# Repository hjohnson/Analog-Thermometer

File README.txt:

PHYS 320 Final Project: Thermometer. 
Harry Johnson
12/17/11
CC BY/SA 3.0

	These circuits are a paired temperature probe and analog panel meter to display said temperature.
 	
	On the probe side, a 2n3904 NPN transistor is used in saturation, where the Base-Emitter junction is essentially a diode. Silicon diodes in saturation have a fairly linear -2.2mV/ºC temperature coefficient. The forward voltage is also dependent on the collector current of the transistor, so the transistor is immersed in ice water to cool it to 0ºC and a potentiometer is used to calibrate the forward voltage to equal a reference voltage formed by R1 and R2. When this is done, the op amp will output 0 volts when the temperature is 0ºC. Next, a second potentiometer is used to calibrate the gain of the op amp circuit so an increase in 1ºC results in a voltage output increase of 100mV.

	On the panel meter side, a 0-100mA ammeter driven by a standard op amp current source is used to display 0-100ºC.

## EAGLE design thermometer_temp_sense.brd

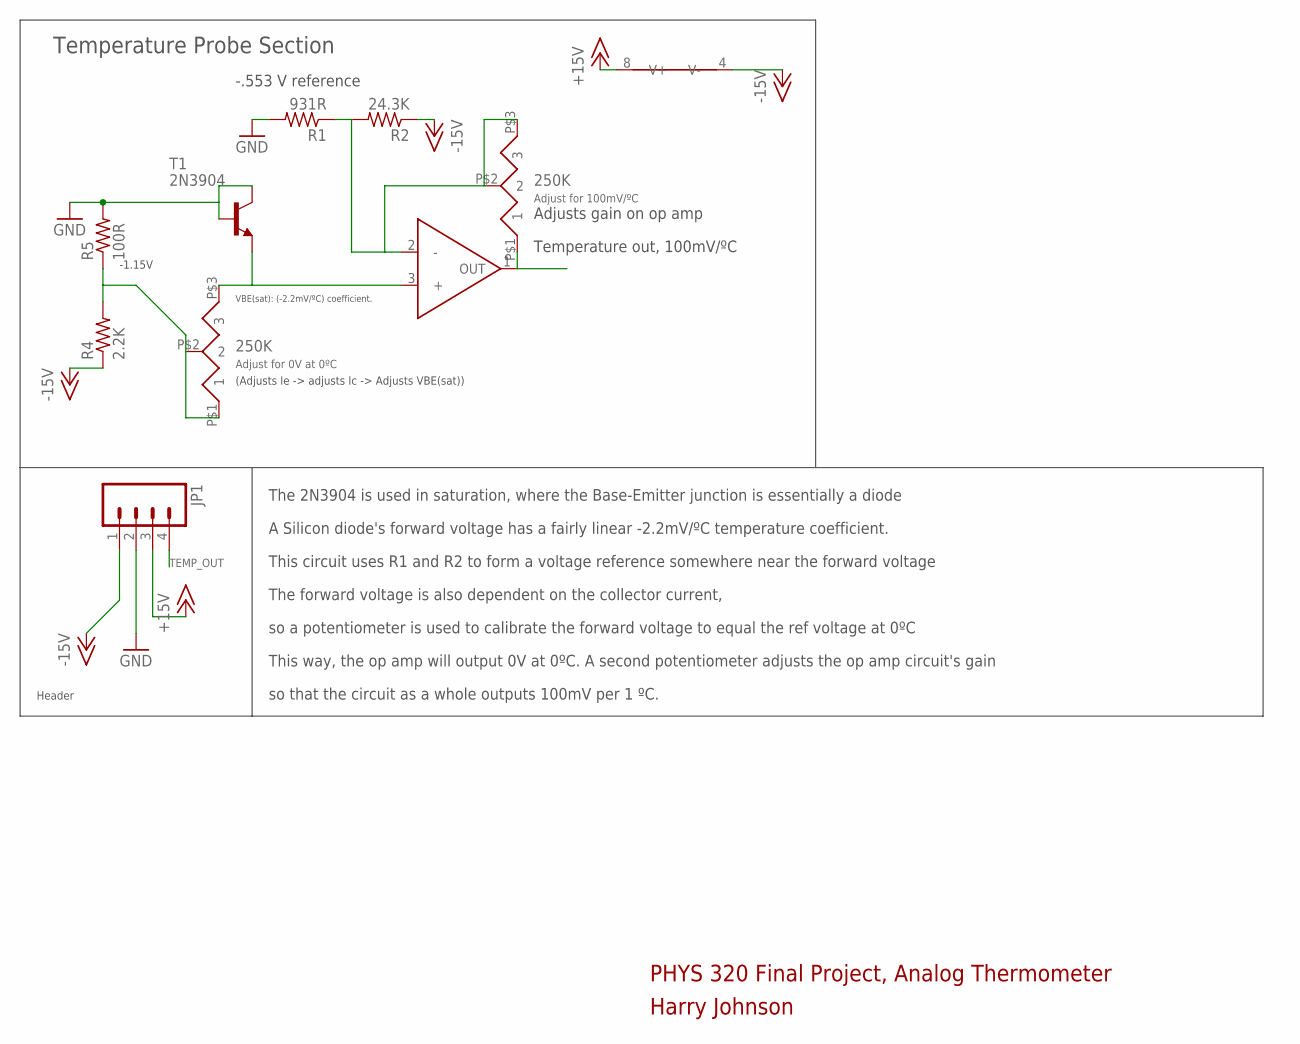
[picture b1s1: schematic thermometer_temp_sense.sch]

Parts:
JP1: M04PTH; 1X04
R1: 931R; 0207/10
R2: 24.3K; 0207/10
R4: 2.2K; 0207/10
R5: 100R; 0207/10
T1: 2N3904; TO92-EBC-OVAL
U$1: TS522IN; DIL08
U$2, U$3: 250K; PV36Y254C01B00

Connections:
+15V: JP1.3, U$1.8 (V+)
-15V: JP1.1, R2.1, R4.1, U$1.4 (V-)
GND: JP1.2, R1.2, R5.2, T1.B, T1.C
unnamed: R1.1, R2.2, U$1.2 (-), U$3.P$2 (2), U$3.P$3 (3)
unnamed: R4.2, R5.1, U$2.P$1 (1), U$2.P$2 (2)
unnamed: T1.E, U$1.3 (+), U$2.P$3 (3)
TEMP_OUT: JP1.4, U$1.1 (OUT), U$3.P$1 (1)

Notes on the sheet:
250K
Adjust for 100mV/ºC
Adjust for 0V at 0ºC
Temperature out, 100mV/ºC
-.553 V reference
VBE(sat): (-2.2mV/ºC) coefficient.
Temperature Probe Section
(Adjusts Ie -> adjusts Ic -> Adjusts VBE(sat))
-1.15V
Header
Harry Johnson
PHYS 320 Final Project, Analog Thermometer
Adjusts gain on op amp
The 2N3904 is used in saturation, where the Base-Emitter junction is essentially a diode
A Silicon diode's forward voltage has a fairly linear -2.2mV/ºC temperature coefficient.
This circuit uses R1 and R2 to form a voltage reference somewhere near the forward voltage
The forward voltage is also dependent on the collector current,
so a potentiometer is used to calibrate the forward voltage to equal the ref voltage at 0ºC
This way, the op amp will output 0V at 0ºC. A second potentiometer adjusts the op amp circuit's gain
so that the circuit as a whole outputs 100mV per 1 ºC.

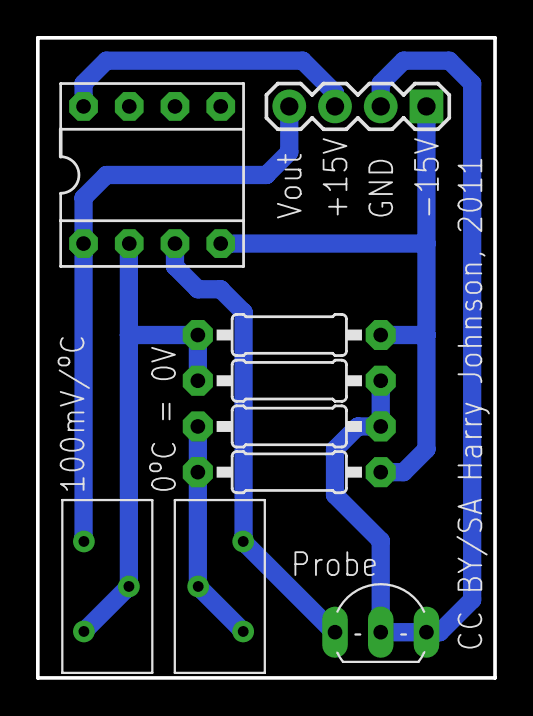
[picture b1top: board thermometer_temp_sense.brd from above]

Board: 2 copper layers, 25.4 x 35.6 mm, 9 parts (0 on the bottom side), 7 nets.

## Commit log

2011-12-18 Added all files.

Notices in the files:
thermometer_temp_sense.brd:
CC BY/SA Harry Johnson, 2011
